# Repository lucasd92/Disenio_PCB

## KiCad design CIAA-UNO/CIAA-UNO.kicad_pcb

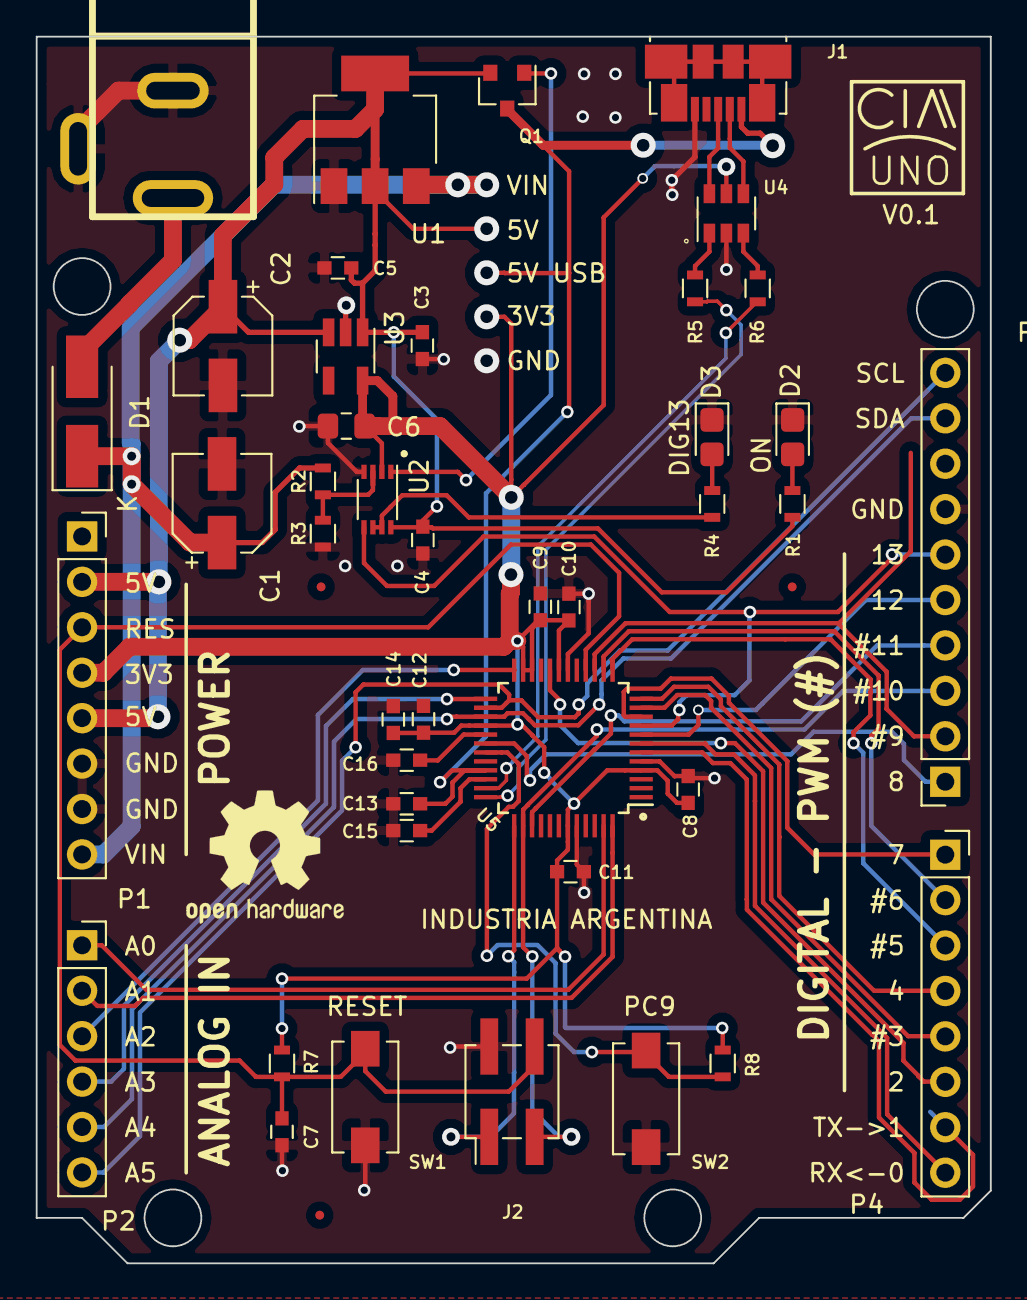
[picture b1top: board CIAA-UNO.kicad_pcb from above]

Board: 2 copper layers, 53.3 x 68.6 mm, 45 parts (0 on the bottom side), 42 nets.

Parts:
C1, C2: 47uF; CP_Elec_5x5.3
C3, C4: 0.1 uF; C_0603
C5: 1uF; C_0603
C6: 2.2uF; C_0805_2012Metric_Pad1.15x1.40mm_HandSolder
C7, C15, C16: 1u; C_0603
C8, C9, C10, C11, C12: 100n; C_0603
C13: 4.7u; C_0603
C14: 10u; C_0603
CON1: BARREL_JACK; dc_socket
D1: DIODE; D_SMA_Handsoldering
D2, D3: LED; LED_0805_2012Metric_Castellated
F1, F2, F3: Fiducial; Fiducial_0.5mm_Dia_1mm_Outer
J1: USB_OTG; USB_Micro-B_Molex_47346-0001
J2: SWD; Pin_Header_Straight_2x02_Pitch2.54mm_SMD
P1: Power Header; PinSocket_1x08_P2.54mm_Vertical
P2: Analog Header; PinSocket_1x06_P2.54mm_Vertical
P3: Digital Header 02; PinSocket_1x10_P2.54mm_Vertical
P4: Digital Header 01; PinSocket_1x08_P2.54mm_Vertical
Q1: FDN340P; SOT-23
R1, R4: 510; R_0603
R2, R3: 10K; R_0603
R5, R6: 15R; R_0603
R7, R8: 1K; R_0603
SW1, SW2: reset; SW_SPST_EVQPE1
U1: LD1117S50TR; SOT-223-3_TabPin2
U2: LMV358IDGKR; VSSOP-8_2.3x2mm_P0.5mm
U3: LP2985-33DBVR; SOT-23-5_HandSoldering
U4: USBLC6-2; SOT-23-6
U5: EFM32HG-48LQFP; LQFP-48_7x7mm_Pitch0.5mm

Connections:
3V3_LDO: C6.1, C8.1, C9.1, C10.2, C11.2, C12.1, C14.1, P1.4, R7.1, R8.1, U2.2, U3.5, U4.5, U5.4, U5.19, U5.22, U5.23, U5.28, U5.43
5V_LDO: C2.1, C3.1, C4.2, C5.1, P1.2, P1.5, Q1.2, R1.2, U1.2, U2.8, U3.1, U3.3
/EFM32HG-48LQFP/328P_RESET: C7.2, J2.4, P1.3, R7.2, SW1.2, U5.16
/EFM32HG-48LQFP/ARD_AN0: P2.1, U5.47
/EFM32HG-48LQFP/ARD_AN1: P2.2, U5.48
/EFM32HG-48LQFP/ARD_AN2: P2.3, U5.24
/EFM32HG-48LQFP/ARD_AN3: P2.4, U5.25
/EFM32HG-48LQFP/ARD_AN4/SDA: P2.5, P3.9, U5.27
/EFM32HG-48LQFP/ARD_AN5/SCL: P2.6, P3.10, U5.26
/EFM32HG-48LQFP/ARD_DIG0: P4.8, U5.7
/EFM32HG-48LQFP/ARD_DIG1: P4.7, U5.6
/EFM32HG-48LQFP/ARD_DIG2: P4.6, U5.20
/EFM32HG-48LQFP/ARD_DIG3: P4.5, U5.11
/EFM32HG-48LQFP/ARD_DIG4: P4.4, U5.12
/EFM32HG-48LQFP/ARD_DIG5: P4.3, U5.13
/EFM32HG-48LQFP/ARD_DIG6: P4.2, U5.14
/EFM32HG-48LQFP/ARD_DIG7: P4.1, U5.10
/EFM32HG-48LQFP/ARD_DIG8: P3.1, U5.30
/EFM32HG-48LQFP/ARD_DIG9: P3.2, U5.15
/EFM32HG-48LQFP/ARD_DIG10/SPI_SS: J2.3, P3.3, U5.38
/EFM32HG-48LQFP/ARD_DIG11/SPI_MOSI: P3.4, U5.39
/EFM32HG-48LQFP/ARD_DIG12/SPI_MISO: P3.5, U5.8
/EFM32HG-48LQFP/ARD_DIG13/SPI_SCK: P3.6, U2.5, U5.9
/EFM32HG-48LQFP/PC9: R8.2, SW2.2, U5.31
/EFM32HG-48LQFP/PF0/SWCLK: J2.1, U5.37
/EFM32HG-48LQFP/USB_D+: R5.2, U5.36
/EFM32HG-48LQFP/USB_D-: R6.2, U5.35
/USB Interface/B_USB+: J1.3, U4.6
/USB Interface/B_USB-: J1.2, U4.4
GND: C1.2, C2.2, C3.2, C4.1, C5.2, C6.2, C7.1, C8.2, C9.2, C10.1, C11.1, C12.2, C13.2, C14.2, C15.2, C16.2, CON1.2, CON1.MP, D2.1, D3.1, J1.5, J2.2, P1.6, P1.7, P3.7, R3.1, SW1.1, SW2.1, U1.1, U2.4, U3.2, U4.2, U5.5, U5.18, U5.44
unnamed: C15.1, U5.34
unnamed: C16.1, U5.29
unnamed: CON1.1, D1.2
unnamed: D2.2, R1.1
unnamed: D3.2, R4.2
unnamed: Q1.1, U2.1
unnamed: R2.1, R3.2, U2.3
unnamed: R4.1, U2.6, U2.7
unnamed: R5.1, U4.1
unnamed: R6.1, U4.3
USBVCC: C13.1, J1.1, Q1.3, U5.33
Vin: C1.1, D1.1, P1.8, R2.2, U1.3

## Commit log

2018-09-23 Revisión 0 del esquemático
2018-09-23 Eliminado archivo readme
2018-10-07 Diseño del PCB
    Faltan fiduciales, comentarios y rótulo.
2018-10-08 Modificaciones menores
    Se agregó el conector de alimentación, fiduciales y logos. Falta comentarios con datos de fabricación.
2018-10-12 Detalles finales
    Agregados comentarios de fabricación
2018-11-19 Revisión 2
    Se tomaron en cosideración las correcciones y se modificó para cumplir con las consignas.
